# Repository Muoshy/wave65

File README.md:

# wave65
discipline65 inspired keyboard

  - QMK firmware
  - Acrylic sandwich case
  - Encoder support
  - VIA-configurable
  
## Schematic
Standard ATMega32u4 setup with Wurth/Amphenol USB-C connector

## PCB

## Case
WIP

## Software
Running on QMK firmware. Use QMK Toolbox to flash with provided HEX file.
Then use VIA configurator to configure keybinds.
For further customization (encoder keycodes), setup a QMK build environment and compile your own HEX files.

## Flashing
  - Download and open QMK Toolbox
  - Select HEX file
  - Choose ATMega32u4 as microcontroller
  - Push reset button on board and then press flash button in toolbox.

## Keybinds
  - Download and install VIA Configurator
  - Open VIA and go to File->Import Keymap
  - Select the keymap.json file
  - Plug in the keyboard

## BOM
WIP

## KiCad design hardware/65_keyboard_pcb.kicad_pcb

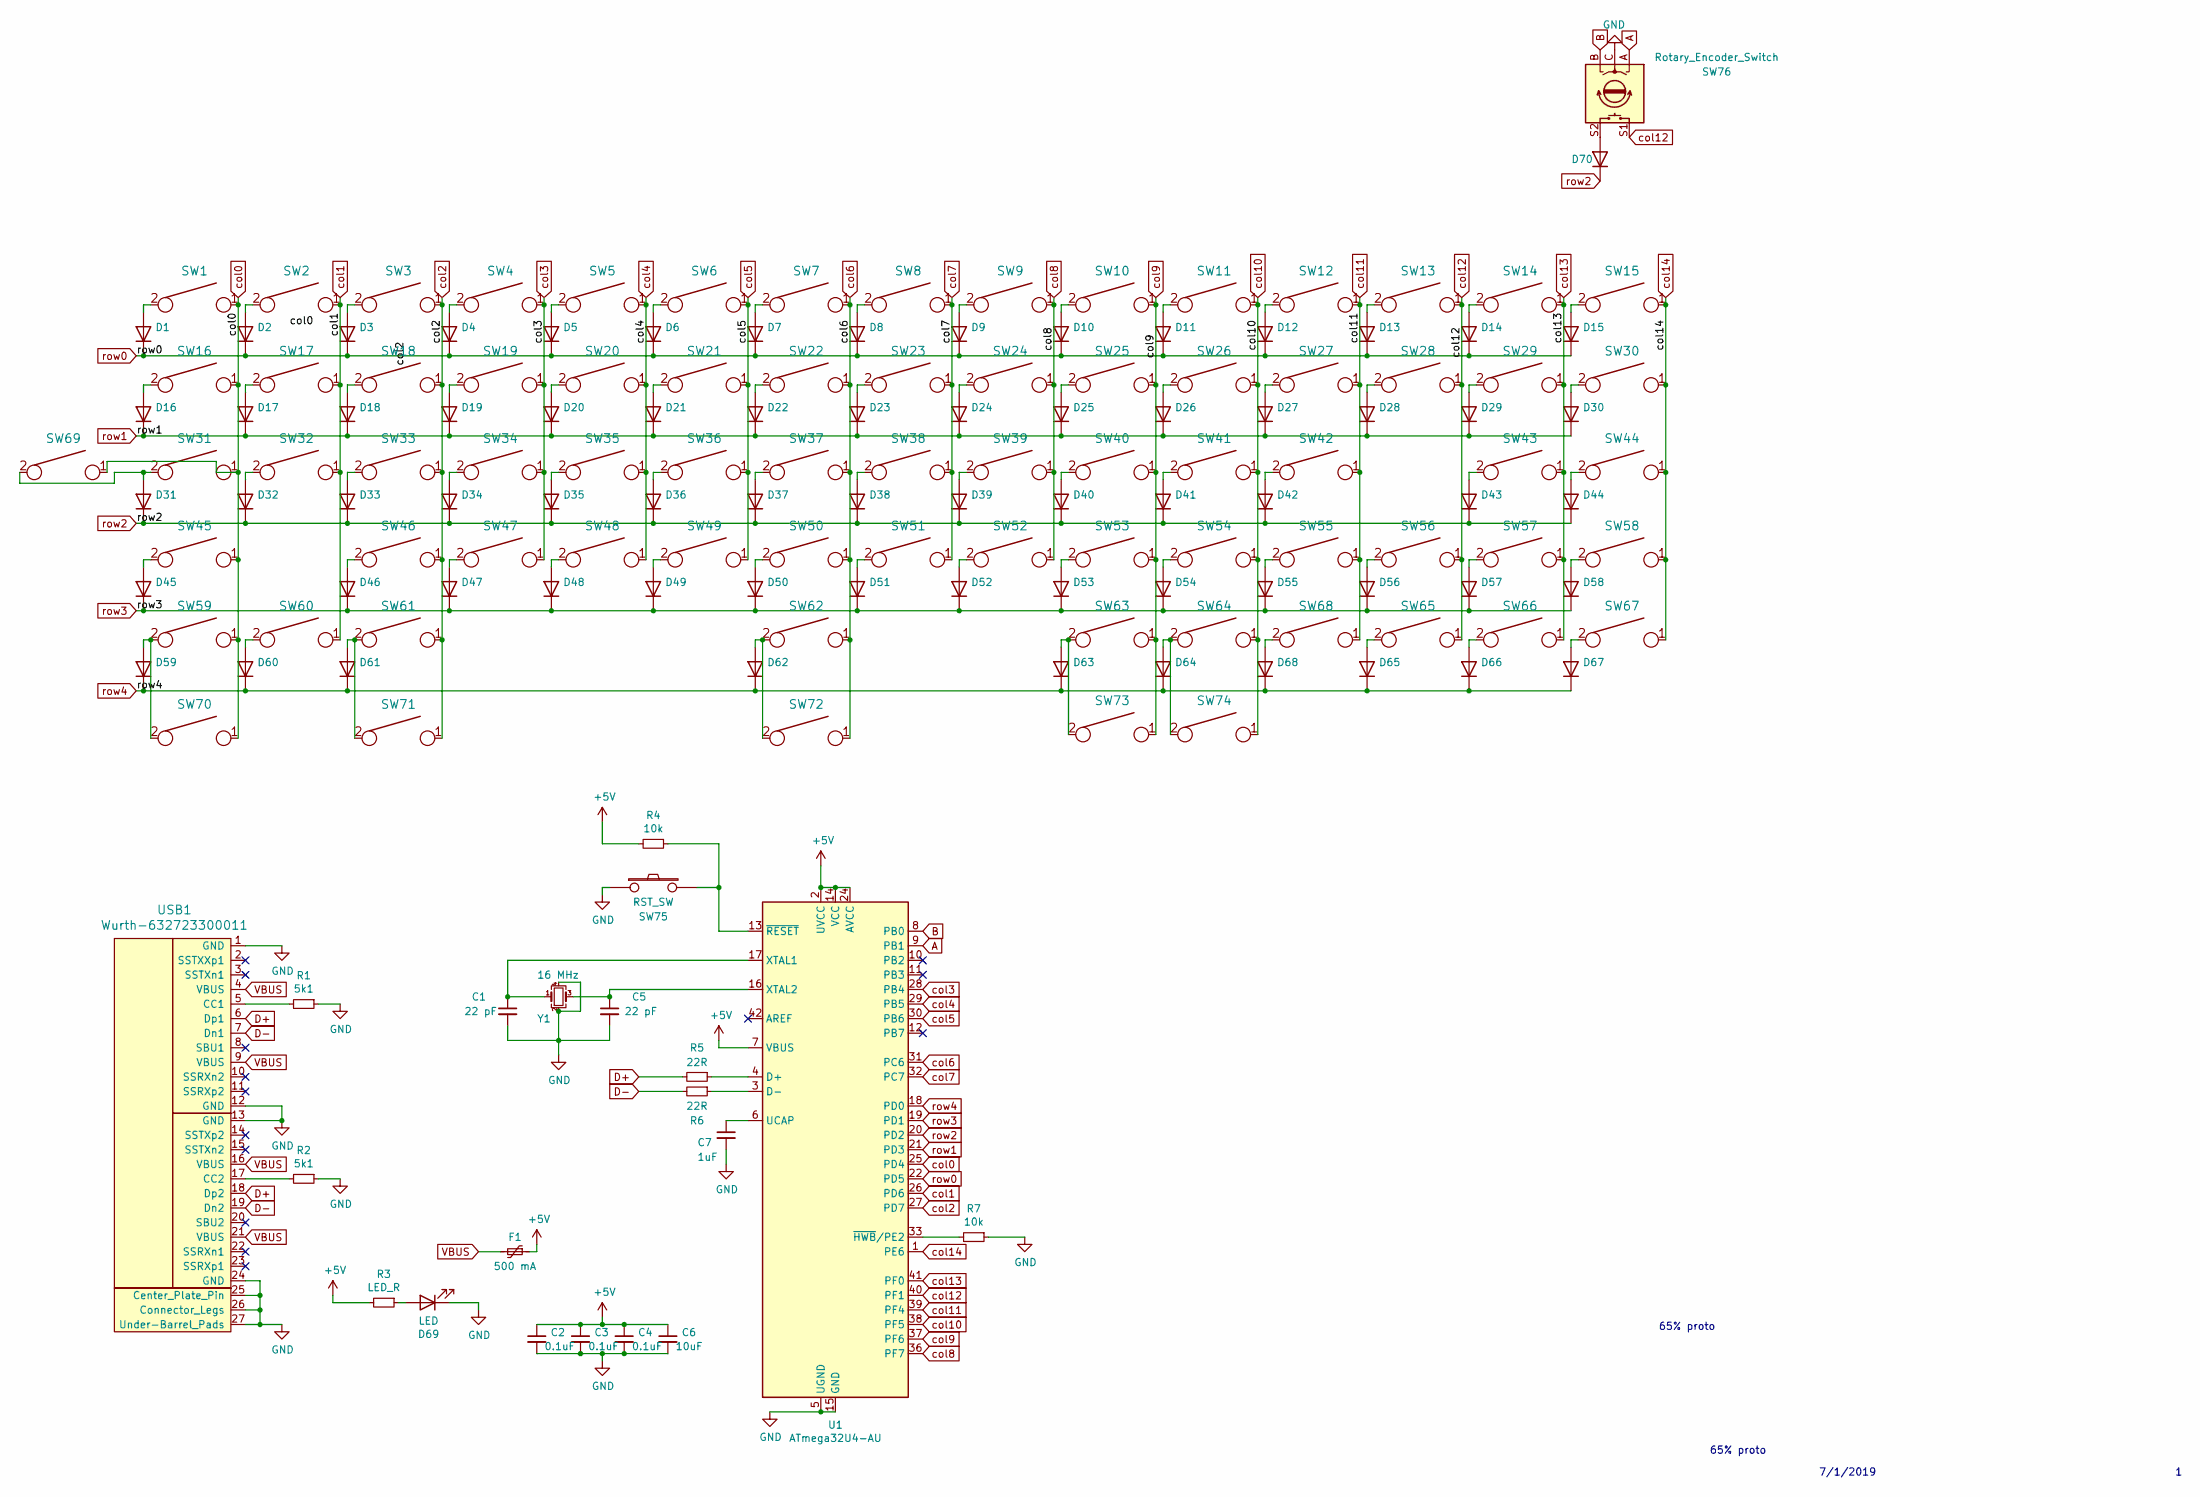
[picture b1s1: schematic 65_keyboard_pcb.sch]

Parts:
C1, C5: 22 pF; C_0603_1608Metric_Pad1.05x0.95mm_HandSolder
C2, C3, C4: 0.1uF; C_0603_1608Metric_Pad1.05x0.95mm_HandSolder
C6: 10uF; C_0603_1608Metric_Pad1.05x0.95mm_HandSolder
C7: 1uF; C_0603_1608Metric_Pad1.05x0.95mm_HandSolder
D1, D2, D3, D4, D5, D6, D7, D8, D9, D10, D11, D12, D13, D14, D15, D16, D17, D18, D19, D20, D21, D22, D23, D24, D25, D26, D27, D28, D29, D30, D31, D32, D33, D34, D35, D36, D37, D38, D39, D40, D41, D42, D43, D44, D45, D46, D47, D48, D49, D50, D51, D52, D53, D54, D55, D56, D57, D58, D59, D60, D61, D62, D63, D64, D65, D66, D67, D68, D70: D_MiniMELF
D69: LED; LED_1206_3216Metric_Pad1.42x1.75mm_HandSolder
F1: 500 mA; Fuse_1206_3216Metric_Pad1.42x1.75mm_HandSolder
R1, R2: 5k1; R_0603_1608Metric_Pad1.05x0.95mm_HandSolder
R3: LED_R; R_0603_1608Metric_Pad1.05x0.95mm_HandSolder
R4, R7: 10k; R_0603_1608Metric_Pad1.05x0.95mm_HandSolder
R5, R6: 22R; R_0603_1608Metric_Pad1.05x0.95mm_HandSolder
SW1, SW2, SW3, SW4, SW5, SW6, SW7, SW8, SW9, SW10, SW11, SW12, SW13, SW15, SW17, SW18, SW19, SW20, SW21, SW22, SW23, SW24, SW25, SW26, SW27, SW28, SW30, SW32, SW33, SW34, SW35, SW36, SW37, SW38, SW39, SW40, SW41, SW42, SW44, SW46, SW47, SW48, SW49, SW50, SW51, SW52, SW53, SW54, SW55, SW57, SW58, SW62, SW65, SW66, SW67, SW68, SW72: KEYSW; SW_Cherry_MX1A_1.00u_PCB-NOSCREEN
SW14: KEYSW; SW_Cherry_MX1A_2.00u_PCBNOSCREEN
SW16, SW29, SW70, SW71, SW73, SW74: KEYSW; SW_Cherry_MX1A_1.50u_PCBNOSCREEN
SW31, SW56: KEYSW; SW_Cherry_MX1A_1.75u_PCBNOSCREEN
SW43, SW45: KEYSW; SW_Cherry_MX1A_2.25u_PCBNOSCREEN
SW59, SW60, SW61, SW63, SW64, SW69: KEYSW; SW_Cherry_MX1A_1.25u_PCBNOSCREEN
SW75: RST_SW; SW_PTS525SM15SMTR2LFS
SW76: Rotary_Encoder_Switch; RotaryEncoder_Alps_EC11E-Switch_Vertical_H20mm
U1: ATmega32U4-AU; TQFP-44_10x10mm_P0.8mm
USB1: Wurth-632723300011; Wurth-632723300011-HandSoldering
Y1: 16 MHz; Crystal_SMD_5032-4Pin_5.0x3.2mm

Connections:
+5V: C2.1, C3.1, C4.1, C6.1, F1.1, R3.2, R4.2, U1.2 (UVCC), U1.7 (VBUS), U1.14 (VCC), U1.24 (AVCC), U1.34 (VCC), U1.44 (AVCC)
A: SW76.A, U1.9 (PB1)
B: SW76.B, U1.8 (PB0)
D+: R5.2, USB1.6 (Dp1), USB1.18 (Dp2); also elsewhere on the board
D-: R6.2, USB1.7 (Dn1), USB1.19 (Dn2); also elsewhere on the board
GND: C1.2, C2.2, C3.2, C4.2, C5.2, C6.2, C7.2, D69.1 (K), R1.1, R2.1, R7.1, SW75.1, SW76.C, U1.5 (UGND), U1.15 (GND), U1.23 (GND), U1.35 (GND), U1.43 (GND), USB1.1 (GND), USB1.12 (GND), USB1.13 (GND), USB1.24 (GND), USB1.25 (Center_Plate_Pin), USB1.26 (Connector_Legs), USB1.27 (Under-Barrel_Pads), Y1.2, Y1.4; also elsewhere on the board
unnamed: C1.1, U1.17 (XTAL1), Y1.1
unnamed: C5.1, U1.16 (XTAL2), Y1.3
unnamed: C7.1, U1.6 (UCAP)
unnamed: D1.2 (A), SW1.2
unnamed: D2.2 (A), SW2.2
unnamed: D3.2 (A), SW3.2
unnamed: D4.2 (A), SW4.2
unnamed: D5.2 (A), SW5.2
unnamed: D6.2 (A), SW6.2
unnamed: D7.2 (A), SW7.2
unnamed: D8.2 (A), SW8.2
unnamed: D9.2 (A), SW9.2
unnamed: D10.2 (A), SW10.2
unnamed: D11.2 (A), SW11.2
unnamed: D12.2 (A), SW12.2
unnamed: D13.2 (A), SW13.2
unnamed: D14.2 (A), SW14.2
unnamed: D15.2 (A), SW15.2
unnamed: D16.2 (A), SW16.2
unnamed: D17.2 (A), SW17.2
unnamed: D18.2 (A), SW18.2
unnamed: D19.2 (A), SW19.2
unnamed: D20.2 (A), SW20.2
unnamed: D21.2 (A), SW21.2
unnamed: D22.2 (A), SW22.2
unnamed: D23.2 (A), SW23.2
unnamed: D24.2 (A), SW24.2
unnamed: D25.2 (A), SW25.2
unnamed: D26.2 (A), SW26.2
unnamed: D27.2 (A), SW27.2
unnamed: D28.2 (A), SW28.2
unnamed: D29.2 (A), SW29.2
unnamed: D30.2 (A), SW30.2
unnamed: D31.2 (A), SW31.2, SW69.2
unnamed: D32.2 (A), SW32.2
unnamed: D33.2 (A), SW33.2
unnamed: D34.2 (A), SW34.2
unnamed: D35.2 (A), SW35.2
unnamed: D36.2 (A), SW36.2
unnamed: D37.2 (A), SW37.2
unnamed: D38.2 (A), SW38.2
unnamed: D39.2 (A), SW39.2
unnamed: D40.2 (A), SW40.2
unnamed: D41.2 (A), SW41.2
unnamed: D42.2 (A), SW42.2
unnamed: D43.2 (A), SW43.2
unnamed: D44.2 (A), SW44.2
unnamed: D45.2 (A), SW45.2
unnamed: D46.2 (A), SW46.2
unnamed: D47.2 (A), SW47.2
unnamed: D48.2 (A), SW48.2
unnamed: D49.2 (A), SW49.2
unnamed: D50.2 (A), SW50.2
unnamed: D51.2 (A), SW51.2
unnamed: D52.2 (A), SW52.2
unnamed: D53.2 (A), SW53.2
unnamed: D54.2 (A), SW54.2
unnamed: D55.2 (A), SW55.2
unnamed: D56.2 (A), SW56.2
unnamed: D57.2 (A), SW57.2
unnamed: D58.2 (A), SW58.2
unnamed: D59.2 (A), SW59.2, SW70.2
unnamed: D60.2 (A), SW60.2
unnamed: D61.2 (A), SW61.2, SW71.2
unnamed: D62.2 (A), SW62.2, SW72.2
unnamed: D63.2 (A), SW63.2, SW73.2
unnamed: D64.2 (A), SW64.2, SW74.2
unnamed: D65.2 (A), SW65.2
unnamed: D66.2 (A), SW66.2
unnamed: D67.2 (A), SW67.2
unnamed: D68.2 (A), SW68.2
unnamed: D69.2 (A), R3.1
unnamed: D70.2 (A), SW76.S2
unnamed 79: R1.2, USB1.5 (CC1); also elsewhere on the board
unnamed 80: R2.2, USB1.17 (CC2); also elsewhere on the board
unnamed: R4.1, SW75.2, U1.13 (~RESET)
unnamed: R5.1, U1.4 (D+)
unnamed: R6.1, U1.3 (D-)
unnamed: R7.2, U1.33 (~HWB~/PE2)
VBUS: F1.2, USB1.4 (VBUS), USB1.9 (VBUS), USB1.16 (VBUS), USB1.21 (VBUS); also elsewhere on the board
col0: SW1.1, SW16.1, SW31.1, SW45.1, SW59.1, SW69.1, SW70.1, U1.25 (PD4)
col1: SW2.1, SW17.1, SW32.1, SW60.1, U1.26 (PD6)
col2: SW3.1, SW18.1, SW33.1, SW46.1, SW61.1, SW71.1, U1.27 (PD7)
col3: SW4.1, SW19.1, SW34.1, SW47.1, U1.28 (PB4)
col4: SW5.1, SW20.1, SW35.1, SW48.1, U1.29 (PB5)
col5: SW6.1, SW21.1, SW36.1, SW49.1, U1.30 (PB6)
col6: SW7.1, SW22.1, SW37.1, SW50.1, SW62.1, SW72.1, U1.31 (PC6)
col7: SW8.1, SW23.1, SW38.1, SW51.1, U1.32 (PC7)
col8: SW9.1, SW24.1, SW39.1, SW52.1, U1.36 (PF7)
col9: SW10.1, SW25.1, SW40.1, SW53.1, SW63.1, SW73.1, U1.37 (PF6)
col10: SW11.1, SW26.1, SW41.1, SW54.1, SW64.1, SW74.1, U1.38 (PF5)
col11: SW12.1, SW27.1, SW42.1, SW55.1, SW68.1, U1.39 (PF4)
col12: SW13.1, SW28.1, SW56.1, SW65.1, SW76.S1, U1.40 (PF1)
col13: SW14.1, SW29.1, SW43.1, SW57.1, SW66.1, U1.41 (PF0)
col14: SW15.1, SW30.1, SW44.1, SW58.1, SW67.1, U1.1 (PE6)
row0: D1.1 (K), D2.1 (K), D3.1 (K), D4.1 (K), D5.1 (K), D6.1 (K), D7.1 (K), D8.1 (K), D9.1 (K), D10.1 (K), D11.1 (K), D12.1 (K), D13.1 (K), D14.1 (K), D15.1 (K), U1.22 (PD5)
row1: D16.1 (K), D17.1 (K), D18.1 (K), D19.1 (K), D20.1 (K), D21.1 (K), D22.1 (K), D23.1 (K), D24.1 (K), D25.1 (K), D26.1 (K), D27.1 (K), D28.1 (K), D29.1 (K), D30.1 (K), U1.21 (PD3)
row2: D31.1 (K), D32.1 (K), D33.1 (K), D34.1 (K), D35.1 (K), D36.1 (K), D37.1 (K), D38.1 (K), D39.1 (K), D40.1 (K), D41.1 (K), D42.1 (K), D43.1 (K), D44.1 (K), D70.1 (K), U1.20 (PD2)
row3: D45.1 (K), D46.1 (K), D47.1 (K), D48.1 (K), D49.1 (K), D50.1 (K), D51.1 (K), D52.1 (K), D53.1 (K), D54.1 (K), D55.1 (K), D56.1 (K), D57.1 (K), D58.1 (K), U1.19 (PD1)
row4: D59.1 (K), D60.1 (K), D61.1 (K), D62.1 (K), D63.1 (K), D64.1 (K), D65.1 (K), D66.1 (K), D67.1 (K), D68.1 (K), U1.18 (PD0)

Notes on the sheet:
65% proto
7/1/2019

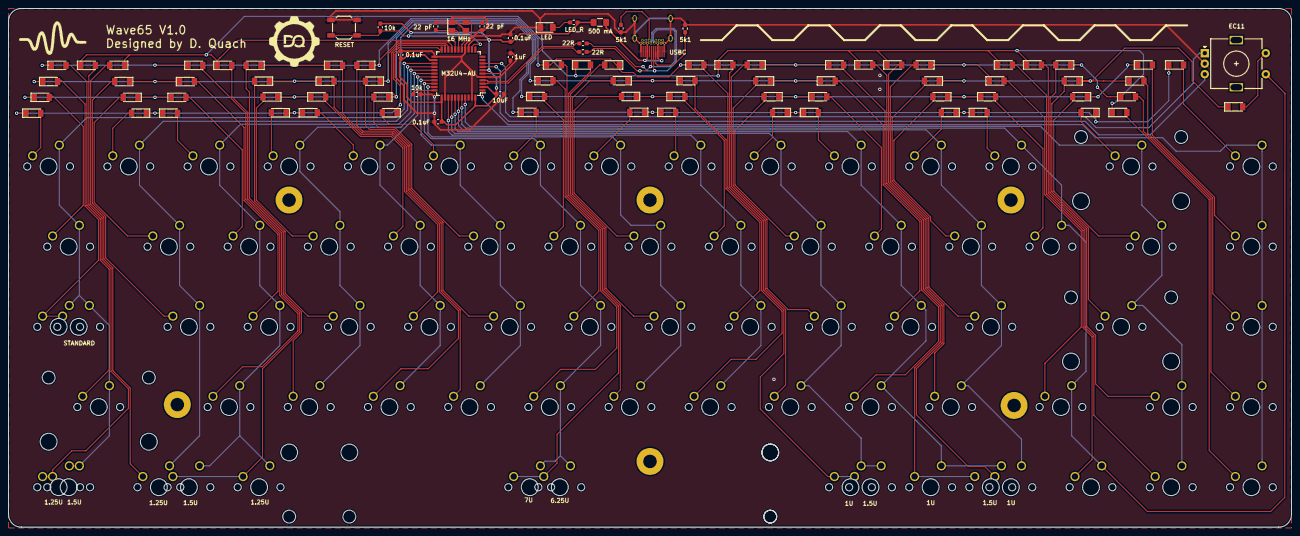
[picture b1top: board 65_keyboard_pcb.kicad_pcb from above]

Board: 2 copper layers, 304.8 x 123.2 mm, 165 parts (0 on the bottom side), 106 nets.

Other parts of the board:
ST62: 7U; MX-7U-Stabilizer
USBC: Wurth-632723300011; Wurth-632723300011-HandSoldering

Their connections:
D+: USBC.6, USBC.18; also elsewhere on the board
D-: USBC.7, USBC.19; also elsewhere on the board
GND: USBC.1, USBC.12, USBC.13, USBC.24, USBC.25, USBC.26; also elsewhere on the board
unnamed 79: USBC.5; also elsewhere on the board
unnamed 80: USBC.17; also elsewhere on the board
VBUS: USBC.4, USBC.9, USBC.16, USBC.21; also elsewhere on the board

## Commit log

2021-03-21 added img
2021-03-21 added software
2021-04-30 Added kicad files
